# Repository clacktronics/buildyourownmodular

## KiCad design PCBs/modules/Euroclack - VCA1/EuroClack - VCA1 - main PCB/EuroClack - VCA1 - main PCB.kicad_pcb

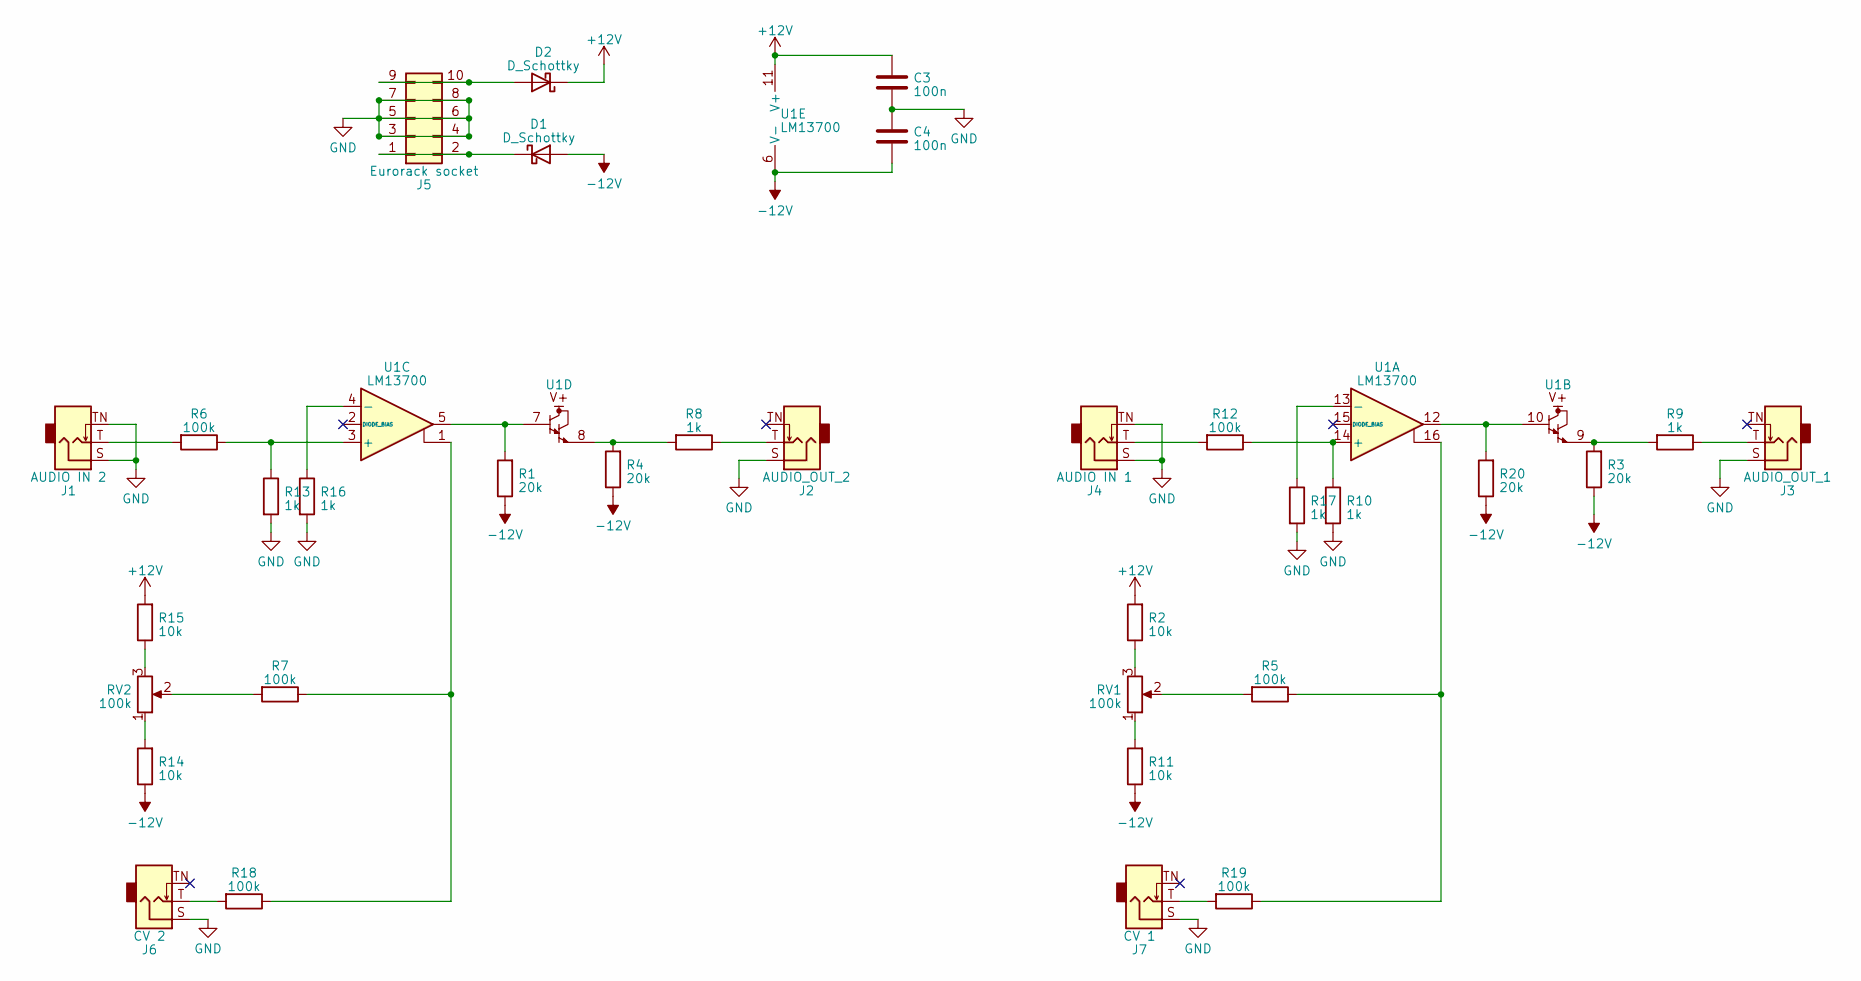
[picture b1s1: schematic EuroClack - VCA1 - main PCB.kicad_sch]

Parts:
C3, C4: 100n; C_TH_Disc_P5.00mm
D1, D2: D_Schottky; D_TH_DO-41_P10.16mm
J1: AUDIO IN 2; Jack_3.5mm_QingPu_WQP-PJ301M-12_Vertical
J2: AUDIO_OUT_2; Jack_3.5mm_QingPu_WQP-PJ301M-12_Vertical
J3: AUDIO_OUT_1; Jack_3.5mm_QingPu_WQP-PJ301M-12_Vertical
J4: AUDIO IN 1; Jack_3.5mm_QingPu_WQP-PJ301M-12_Vertical
J5: Eurorack socket; IDC-Header_2x05_P2.54mm_Vertical
J6: CV 2; Jack_3.5mm_QingPu_WQP-PJ301M-12_Vertical
J7: CV 1; Jack_3.5mm_QingPu_WQP-PJ301M-12_Vertical
R1, R3, R4, R20: 20k; R_Axial_DIN0204_L3.6mm_D1.6mm_P7.62mm_Horizontal
R2, R11, R14, R15: 10k; R_Axial_DIN0204_L3.6mm_D1.6mm_P7.62mm_Horizontal
R5, R6, R7, R12, R18, R19: 100k; R_Axial_DIN0204_L3.6mm_D1.6mm_P7.62mm_Horizontal
R8, R9, R10, R13, R16, R17: 1k; R_Axial_DIN0204_L3.6mm_D1.6mm_P7.62mm_Horizontal
RV1, RV2: 100k; POT_TH_Alps_RK09K_Single_Vertical
U1: LM13700; DIP-16_W7.62mm_LongPads

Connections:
+12V: C3.1, D2.1 (K), R2.2, R15.2, U1.11 (V+)
-12V: C4.2, D1.2 (A), R1.1, R3.1, R4.1, R11.1, R14.1, R20.1, U1.6 (V-)
GND: C3.2, C4.1, J1.S, J1.TN, J2.S, J3.S, J4.S, J4.TN, J5.3, J5.4, J5.5, J5.6, J5.7, J5.8, J6.S, J7.S, R10.2, R13.2, R16.2, R17.2
unnamed: D1.1 (K), J5.1, J5.2
unnamed: D2.2 (A), J5.9, J5.10
unnamed: J1.T, R6.2
unnamed: J2.T, R8.1
unnamed: J3.T, R9.1
unnamed: J4.T, R12.2
unnamed: J6.T, R18.2
unnamed: J7.T, R19.2
unnamed: R1.2, U1.5, U1.7
unnamed: R2.1, RV1.3
unnamed: R3.2, R9.2, U1.9
unnamed: R4.2, R8.2, U1.8
unnamed: R5.2, RV1.2
unnamed: R7.2, RV2.2
unnamed: R11.2, RV1.1
unnamed: R14.2, RV2.1
unnamed: R15.1, RV2.3
unnamed: R7.1, R18.1, U1.1
unnamed: R5.1, R19.1, U1.16
unnamed: R20.2, U1.10, U1.12
unnamed: R10.1, R12.1, U1.14 (+)
unnamed: R17.1, U1.13 (-)
unnamed: R6.1, R13.1, U1.3 (+)
unnamed: R16.1, U1.4 (-)

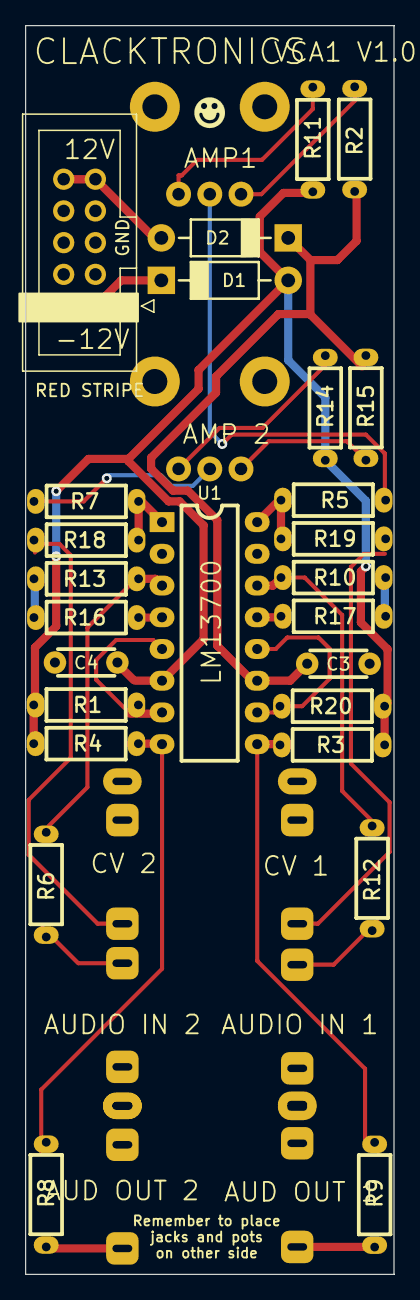
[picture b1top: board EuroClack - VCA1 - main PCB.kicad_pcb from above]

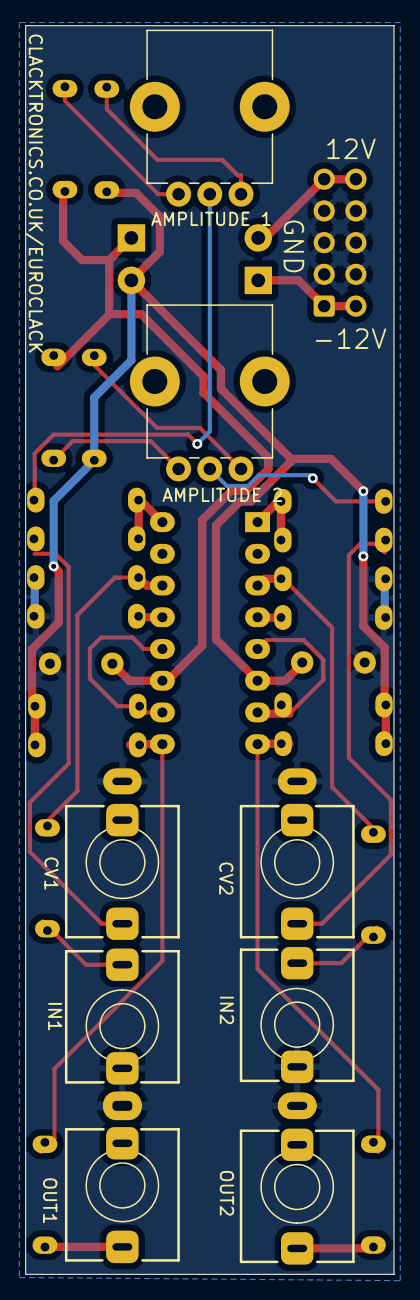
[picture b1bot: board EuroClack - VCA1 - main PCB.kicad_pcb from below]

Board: 2 copper layers, 29.5 x 100.0 mm, 34 parts (8 on the bottom side), 27 nets.
